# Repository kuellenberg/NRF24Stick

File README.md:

# NRF24Stick

nRF24L01+ Test Board

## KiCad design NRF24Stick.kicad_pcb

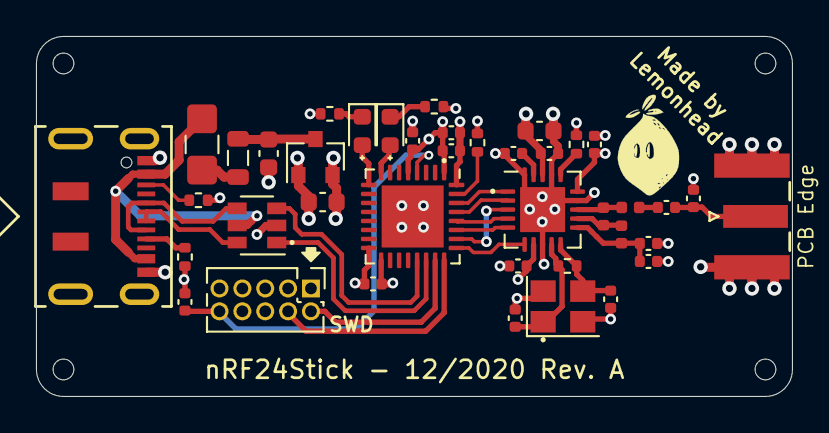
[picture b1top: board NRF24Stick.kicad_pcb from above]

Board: 4 copper layers, 42.0 x 20.0 mm, 44 parts (0 on the bottom side), 34 nets.

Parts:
C1: 1uF; C_0402_1005Metric
C2, C3, C4, C7: 100nF; C_0402_1005Metric
C5, C6, C18: 10uF; C_0603_1608Metric
C8, C9: 10nF; C_0402_1005Metric
C10: 33nF; C_0402_1005Metric
C11: 1nF; C_0402_1005Metric
C12, C14: 12pF; C_0402_1005Metric
C13: 2.2nF; C_0402_1005Metric
C15: 4.7pF; C_0402_1005Metric
C16: 1.5pF; C_0402_1005Metric
C17: 1.0pF; C_0402_1005Metric
F1: 100mA; Fuse_1206_3216Metric_Castellated
FB1: 100R @ 100MHz; L_0805_2012Metric
H1, H2, H3, H4: MountingHole; JLCPCB Tooling Hole
J1: SWD; PinHeader_2x05_P1.27mm_Vertical
J2: USB_C_Receptacle_USB2.0; DX07S016JA3R1500
J3: SMA; SMA_Samtec_SMA-J-P-H-ST-EM1_EdgeMount
L1: 8.2nH; L_0402_1005Metric
L2: 2.7nH; L_0402_1005Metric
L3: 3.9nH; L_0402_1005Metric
LD1: GR; LED_0603_1608Metric
LD2: YE; LED_0603_1608Metric
R1, R2: 1k; R_0402_1005Metric
R3, R4: 22k; R_0402_1005Metric
R5: 1M; R_0402_1005Metric
R6, R7: 5k1; R_0402_1005Metric
U1: XC6206P332MR; SOT-23
U2: USBLC6-2SC6; SOT-23-6
U3: STM32L432KBUx; QFN-32-1EP_5x5mm_P0.5mm_EP3.45x3.45mm
U4: nRF24L01P; QFN-20-1EP_4x4mm_P0.5mm_EP2.5x2.5mm
Y1: 16MHz; Crystal_SMD_3225-4Pin_3.2x2.5mm

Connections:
+3V3: C1.1, C2.1, C3.1, C4.1, C6.1, C8.2, C9.2, C11.2, C18.1, J1.1, U1.2, U3.1, U3.5, U3.17, U4.7, U4.15, U4.18
+5V: F1.2, J2.A4, J2.A9, U2.5
/ANT1: L1.1, L2.1, U4.12
/ANT2: L1.2, L3.2, U4.13
/ANT_OUT: C16.1, C17.2, J3.1
/DVDD: C10.2, U4.19
/IREF: R4.1, U4.16
/LED_GR: LD1.2, U3.9
/LED_YE: LD2.2, U3.8
/NRF_CE: U3.30, U4.1
/NRF_CSN: U3.29, U4.2
/NRF_IRQ: U3.25, U4.6
/NRST: C7.2, J1.10, U3.4
/SPI_MISO: U3.27, U4.5
/SPI_MOSI: U3.28, U4.4
/SPI_SCK: U3.26, U4.3
/SWCLK: J1.4, U3.24
/SWDIO: J1.2, U3.23
/USB_CONN_D+: J2.A6, J2.B6, U2.6
/USB_CONN_D-: J2.A7, J2.B7, U2.4
/USB_D+: U2.1, U3.22
/USB_D-: U2.3, U3.21
/VDD_PA: C13.1, C15.1, L2.2, U4.11
/XC1: C14.1, R5.1, U4.10, Y1.3
/XC2: C12.1, R5.2, U4.9, Y1.1
GND: C1.2, C2.2, C3.2, C4.2, C5.2, C6.2, C7.1, C8.1, C9.1, C10.1, C11.1, C12.2, C13.2, C14.2, C15.2, C17.1, C18.2, J1.3, J1.5, J1.9, J2.A1, J2.A12, J3.2, R1.2, R2.2, R3.2, R4.2, R6.1, R7.1, U1.1, U2.2, U3.16, U3.32, U3.33, U4.8, U4.14, U4.17, U4.20, U4.21, Y1.2, Y1.4
unnamed: C5.1, FB1.1, U1.3
unnamed: C16.2, L3.1
unnamed: F1.1, FB1.2
unnamed: J2.A5, R6.2
unnamed: J2.B5, R7.2
unnamed: LD1.1, R1.1
unnamed: LD2.1, R2.1
unnamed: R3.1, U3.31

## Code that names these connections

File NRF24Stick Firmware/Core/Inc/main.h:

/* USER CODE BEGIN Header */
/**
  ******************************************************************************
  * @file           : main.h
  * @brief          : Header for main.c file.
  *                   This file contains the common defines of the application.
  ******************************************************************************
  * @attention
  *
  * <h2><center>&copy; Copyright (c) 2021 STMicroelectronics.
  * All rights reserved.</center></h2>
  *
  * This software component is licensed by ST under BSD 3-Clause license,
  * the "License"; You may not use this file except in compliance with the
  * License. You may obtain a copy of the License at:
  *                        opensource.org/licenses/BSD-3-Clause
  *
  ******************************************************************************
  */
/* USER CODE END Header */

/* Define to prevent recursive inclusion -------------------------------------*/
#ifndef __MAIN_H
#define __MAIN_H

#ifdef __cplusplus
extern "C" {
#endif

/* Includes ------------------------------------------------------------------*/
#include "stm32l4xx_hal.h"

/* Private includes ----------------------------------------------------------*/
/* USER CODE BEGIN Includes */

/* USER CODE END Includes */

/* Exported types ------------------------------------------------------------*/
/* USER CODE BEGIN ET */

/* USER CODE END ET */

/* Exported constants --------------------------------------------------------*/
/* USER CODE BEGIN EC */

/* USER CODE END EC */

/* Exported macro ------------------------------------------------------------*/
/* USER CODE BEGIN EM */

/* USER CODE END EM */

/* Exported functions prototypes ---------------------------------------------*/
void Error_Handler(void);

/* USER CODE BEGIN EFP */

/* USER CODE END EFP */

/* Private defines -----------------------------------------------------------*/
#define LED_YE_Pin GPIO_PIN_2
#define LED_YE_GPIO_Port GPIOA
#define LED_GR_Pin GPIO_PIN_3
#define LED_GR_GPIO_Port GPIOA
#define NRF_IRQ_Pin GPIO_PIN_15
#define NRF_IRQ_GPIO_Port GPIOA
#define NRF_CSN_Pin GPIO_PIN_6
#define NRF_CSN_GPIO_Port GPIOB
#define NRF_CE_Pin GPIO_PIN_7
#define NRF_CE_GPIO_Port GPIOB
/* USER CODE BEGIN Private defines */

/* USER CODE END Private defines */

#ifdef __cplusplus
}
#endif

#endif /* __MAIN_H */

/************************ (C) COPYRIGHT STMicroelectronics *****END OF FILE****/

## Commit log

2021-02-08 Started firmware
